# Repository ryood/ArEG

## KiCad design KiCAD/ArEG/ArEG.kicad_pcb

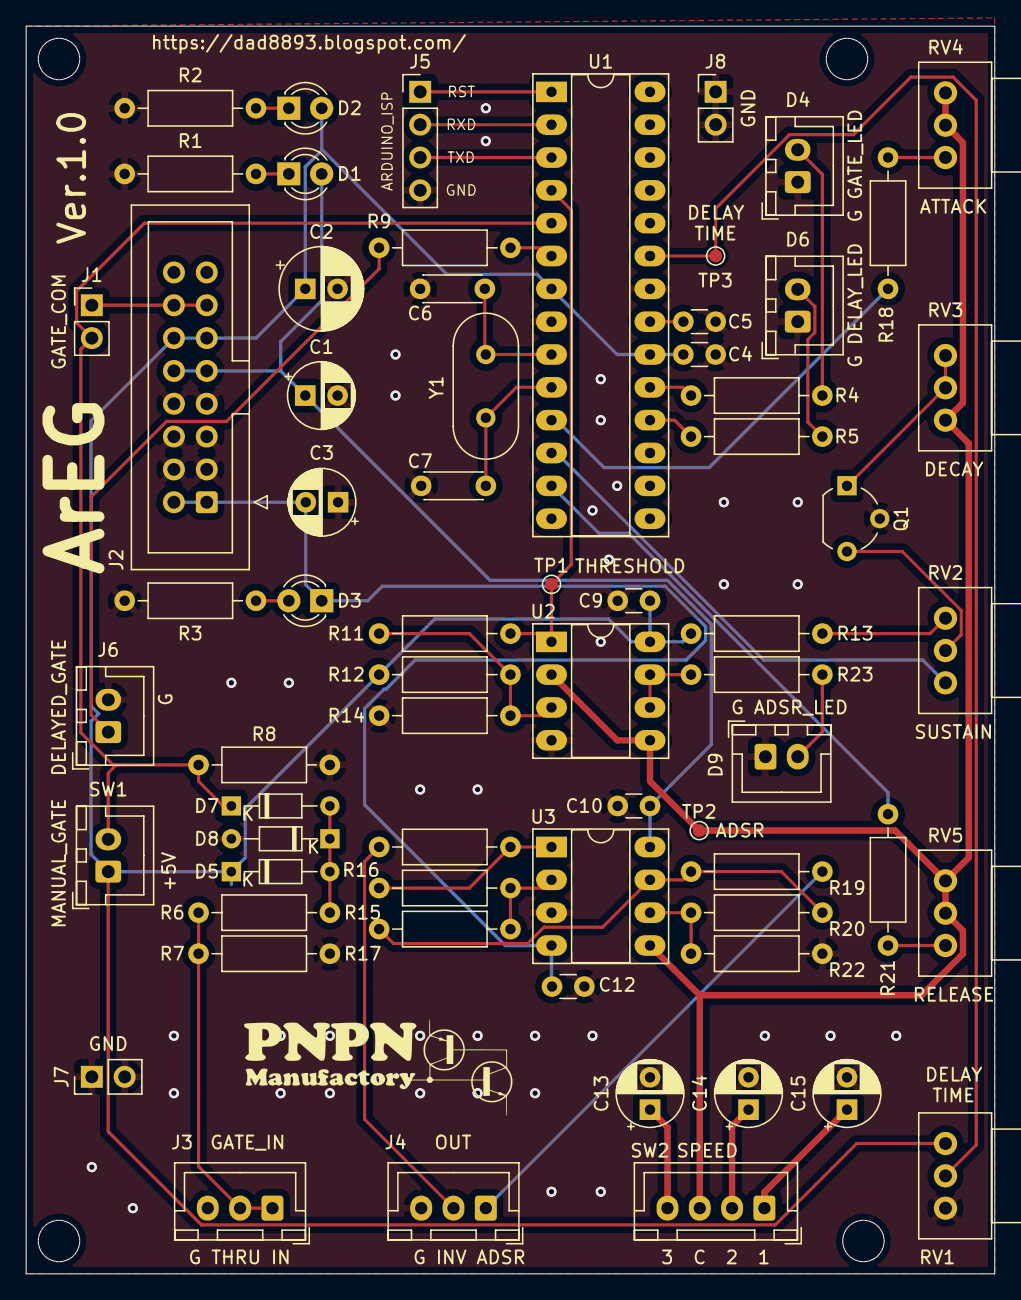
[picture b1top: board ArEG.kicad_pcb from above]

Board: 2 copper layers, 74.9 x 96.5 mm, 71 parts (0 on the bottom side), 46 nets.

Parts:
C1, C3: 47u; CP_Radial_D5.0mm_P2.50mm
C2: 100u; CP_Radial_D6.3mm_P2.50mm
C4, C5, C9, C10, C12: 0.1u; C_Disc_D3.0mm_W1.6mm_P2.50mm
C6, C7: 22p; C_Disc_D4.3mm_W1.9mm_P5.00mm
C13: 10u(C&T); CP_Radial_D5.0mm_P2.50mm
C14: 4.7u(C&T); CP_Radial_D5.0mm_P2.50mm
C15: 1u(C&T); CP_Radial_D5.0mm_P2.50mm
D1: RED; LED_D3.0mm
D2: GREEN; LED_D3.0mm
D3: BLUE; LED_D3.0mm
D4: RED; JST_XH_B2B-XH-A_1x02_P2.50mm_Vertical
D5, D8: 1N4148; D_DO-34_SOD68_P7.62mm_Horizontal
D6: YELLOW; JST_XH_B2B-XH-A_1x02_P2.50mm_Vertical
D7: 1SS106; D_DO-34_SOD68_P7.62mm_Horizontal
D9: GREEN; JST_XH_B2B-XH-A_1x02_P2.50mm_Vertical
H1, H2, H3, H4: MountingHole; MountingHole_3.2mm_M3
J1: GATE_ACTIVE; PinHeader_1x02_P2.54mm_Vertical
J2: ERK_PWR; IDC-Header_2x08_P2.54mm_Vertical
J3: GATE_IN; JST_XH_B3B-XH-A_1x03_P2.50mm_Vertical
J4: OUTPUT; JST_XH_B3B-XH-A_1x03_P2.50mm_Vertical
J5: ArduinoISP; PinHeader_1x04_P2.54mm_Vertical
J6: DELAYED_GATE; JST_XH_B2B-XH-A_1x02_P2.50mm_Vertical
J7, J8: TP_GND; PinHeader_1x02_P2.54mm_Vertical
Q1: 2SA1015; TO-92_Wide
R1, R3, R6: 4.7k; R_Axial_DIN0207_L6.3mm_D2.5mm_P10.16mm_Horizontal
R2, R4, R5, R16, R19, R23: 1k; R_Axial_DIN0207_L6.3mm_D2.5mm_P10.16mm_Horizontal
R7: Open; R_Axial_DIN0207_L6.3mm_D2.5mm_P10.16mm_Horizontal
R8, R15, R17, R22: 100k; R_Axial_DIN0207_L6.3mm_D2.5mm_P10.16mm_Horizontal
R9: 33; R_Axial_DIN0207_L6.3mm_D2.5mm_P10.16mm_Horizontal
R11: 82k; R_Axial_DIN0207_L6.3mm_D2.5mm_P10.16mm_Horizontal
R12: 12k; R_Axial_DIN0207_L6.3mm_D2.5mm_P10.16mm_Horizontal
R13: 22k(C&T); R_Axial_DIN0207_L6.3mm_D2.5mm_P10.16mm_Horizontal
R14: 22k; R_Axial_DIN0207_L6.3mm_D2.5mm_P10.16mm_Horizontal
R18, R21: 150; R_Axial_DIN0207_L6.3mm_D2.5mm_P10.16mm_Horizontal
R20: 82k(C&T); R_Axial_DIN0207_L6.3mm_D2.5mm_P10.16mm_Horizontal
RV1: 50k/B; Potentiometer_Alps_RK09Y11_Single_Horizontal
RV2, RV3: 50k/A; Potentiometer_Alps_RK09Y11_Single_Horizontal
RV4, RV5: 50kA; Potentiometer_Alps_RK09Y11_Single_Horizontal
SW1: MANUAL_GATE; JST_XH_B2B-XH-A_1x02_P2.50mm_Vertical
SW2: Speed; JST_XH_B4B-XH-A_1x04_P2.50mm_Vertical
TP1: TP_Threshold; TestPoint_Pad_D1.0mm
TP2: TP_ADSR; TestPoint_Pad_D1.0mm
TP3: TP_DelayTime; TestPoint_Pad_D1.0mm
U1: ATmega328-PU; DIP-28_W7.62mm_Socket_LongPads
U2: NJM2904; DIP-8_W7.62mm_Socket_LongPads
U3: TL072; DIP-8_W7.62mm_Socket_LongPads
Y1: 16MHz; Crystal_HC18-U_Vertical

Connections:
+5V: C2.1, C4.2, C9.1, D2.2, D5.1, J2.11, J2.12, R12.2, R13.1, RV1.3, SW1.1, U1.7, U1.20, U2.8
+12V: C1.1, C10.1, D1.2, J2.9, J2.10, U3.8
-12V: C3.2, C12.2, D3.1, J2.1, J2.2, U3.4
/ADSR/ADSR_OUT: J4.1, R19.1
/ADSR/INV_OUT: J4.2, R16.1
/RST: J5.1, U1.1
/RXD: J5.2, U1.2
/TXD: J5.3, U1.3
Attack: R18.2, U1.11
Decay: RV2.1, U1.12
Delay_Time: RV1.2, TP3.1, U1.23
Delayed_Gate: R9.2, U1.6
Delayed_LED: R5.2, U1.18
GND: C1.2, C2.2, C3.1, C4.1, C5.1, C6.1, C7.2, C9.2, C10.2, C12.1, C13.2, C14.2, C15.2, D4.1, D6.1, D8.2, D9.1, J2.3, J2.4, J2.5, J2.6, J2.7, J2.8, J3.3, J4.3, J5.4, J6.2, J7.1, J7.2, J8.1, J8.2, Q1.2, R1.2, R2.2, R3.1, R7.1, R8.2, R14.1, R22.2, RV1.1, U1.8, U1.22, U2.4, U3.3
Gate_Com: D7.1, J1.2, R8.1, SW1.2, U1.5
Gate_LED: R4.2, U1.19
unnamed: C5.2, U1.21
unnamed: C6.2, U1.9, Y1.1
unnamed: C7.1, U1.10, Y1.2
unnamed: C13.1, SW2.4
unnamed: C14.1, SW2.2
unnamed: C15.1, SW2.1
unnamed: D1.1, R1.1
unnamed: D2.1, R2.1
unnamed: D3.2, R3.2
unnamed: D4.2, R4.1
unnamed: D5.2, D7.2, D8.1, R6.2
unnamed: D6.2, R5.1
unnamed: D9.2, R23.2
unnamed: J1.1, J2.13, J2.14
unnamed: J3.1, J3.2, R6.1, R7.2
unnamed: J6.1, R9.1
unnamed: Q1.1, RV3.2, RV3.3
unnamed: Q1.3, RV2.2
unnamed: R11.2, R12.1, R14.2, U2.3
unnamed: R13.2, RV2.3
unnamed: R15.1, R16.2, U3.1
unnamed: R15.2, R17.1, U3.2
unnamed: R17.2, R19.2, R20.1, U3.7
unnamed: R18.1, RV4.1
unnamed: R20.2, R22.1, U3.6
unnamed: R21.1, RV5.1
unnamed: R23.1, U2.6, U2.7
unnamed: RV3.1, RV4.2, RV4.3, RV5.2, RV5.3, SW2.3, TP2.1, U2.2, U2.5, U3.5
Release: R21.2, U1.13
Threshold: R11.1, TP1.1, U1.4, U2.1

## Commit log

2021-12-07 入出力端子をまとめる前
2022-01-23 Panel design
2022-05-13 Update schematics
2022-05-13 New panel design
2022-05-23 Fixed firmware bugs
2022-05-23 2nd Unit
